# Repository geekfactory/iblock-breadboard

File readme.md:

# iBlock Breadboard Adapter

Proyecto de EAGLE para fabricar un sencillo adaptador que permite conectar el sistema iBlock a un protoboard. El Adaptador expone los 10 cables a un formato que puede ser usado fácilmente en una protoboard o tarjetas perforadas.

Esta versión se ha realizado con la finalidad de ocupar el mínimo espacio en la tarjeta de circuito impreso, de forma que puedan fabricarse en grandes cantidades a bajo costo.

## Periféricos y características

* Conector estándar de 10 pines IDC-10 con distribución de conector iBlock
* Circuito impreso con superficie minima
* Descompone los pines del conector IDC-10 a dos tiras de pines de 5 contactos cada una 
* Disposición amigable con el protoboard
* Se proporciona alimentación a través del cable IDC-10

## Contenido del repositorio

1. __root__ - Archivos fuente de EAGLE para esta placa
2. __/documents__ - Documentación adicional, hojas de datos de componentes e instrucciones de ensamble
3. __/production__ - Histórico de gerbers enviados a producción
4. __/extras__ - Dibujos técnicos, hardware de montaje adicional y diseños de accesorios relacionados
4. __/firmware__ - Si existe el firmware de prueba o definitivo de esta placa

## Versiones del Hardware

* 1.0 - Versión inicial

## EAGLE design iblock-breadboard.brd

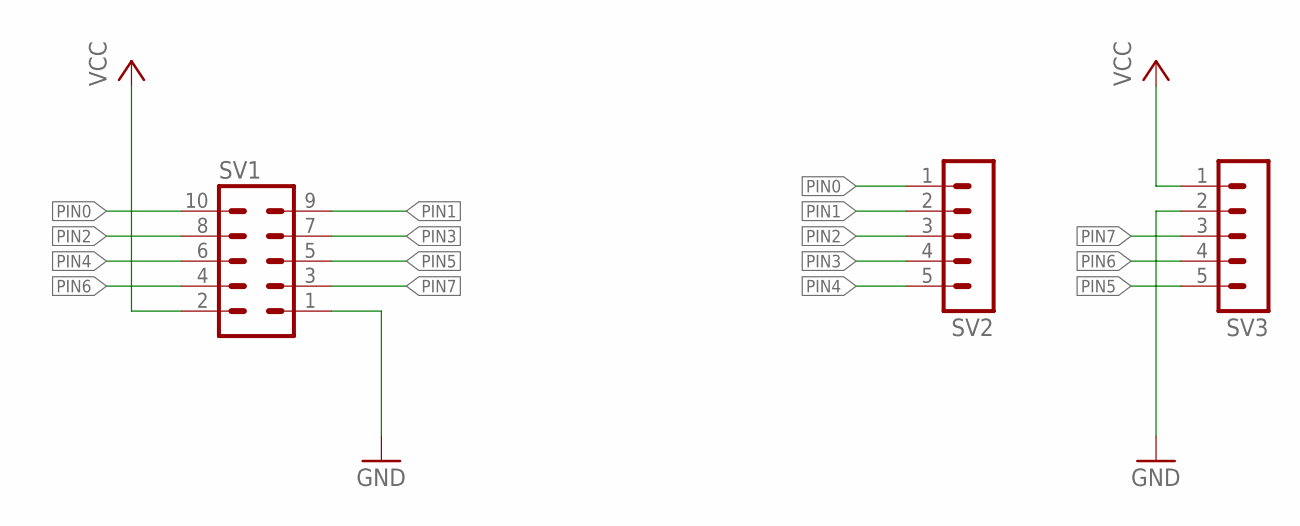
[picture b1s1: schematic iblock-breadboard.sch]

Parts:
SV1: MA05-2
SV2, SV3: MA05-1

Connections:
GND: SV1.1, SV3.2
PIN0: SV1.10, SV2.1
PIN1: SV1.9, SV2.2
PIN2: SV1.8, SV2.3
PIN3: SV1.7, SV2.4
PIN4: SV1.6, SV2.5
PIN5: SV1.5, SV3.5
PIN6: SV1.4, SV3.4
PIN7: SV1.3, SV3.3
VCC: SV1.2, SV3.1

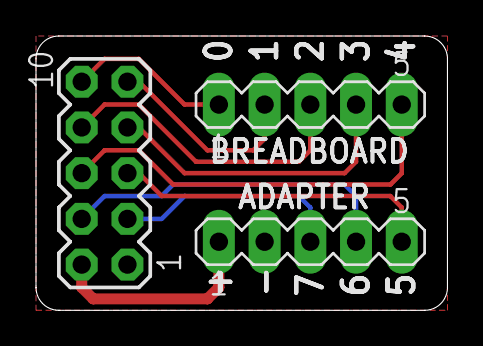
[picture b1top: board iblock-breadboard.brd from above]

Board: 2 copper layers, 22.9 x 15.2 mm, 3 parts (0 on the bottom side), 10 nets.
